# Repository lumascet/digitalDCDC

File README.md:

# Atmel atmega 328p DCDC controller
Arduino Uno Project for digitally controlling DCDC converter with adc & dac over i2c with dotmatrix display.
Utilizes the cheap B3606 analog DCDC converter circuit.

The onboard 4.096V reference in combination with 2 12bit DACs as well as one 4 Channel 16bit ADC enable accurate voltage and current setpoints. 

The graphical interface also features a graph display, showing voltage and current over time.

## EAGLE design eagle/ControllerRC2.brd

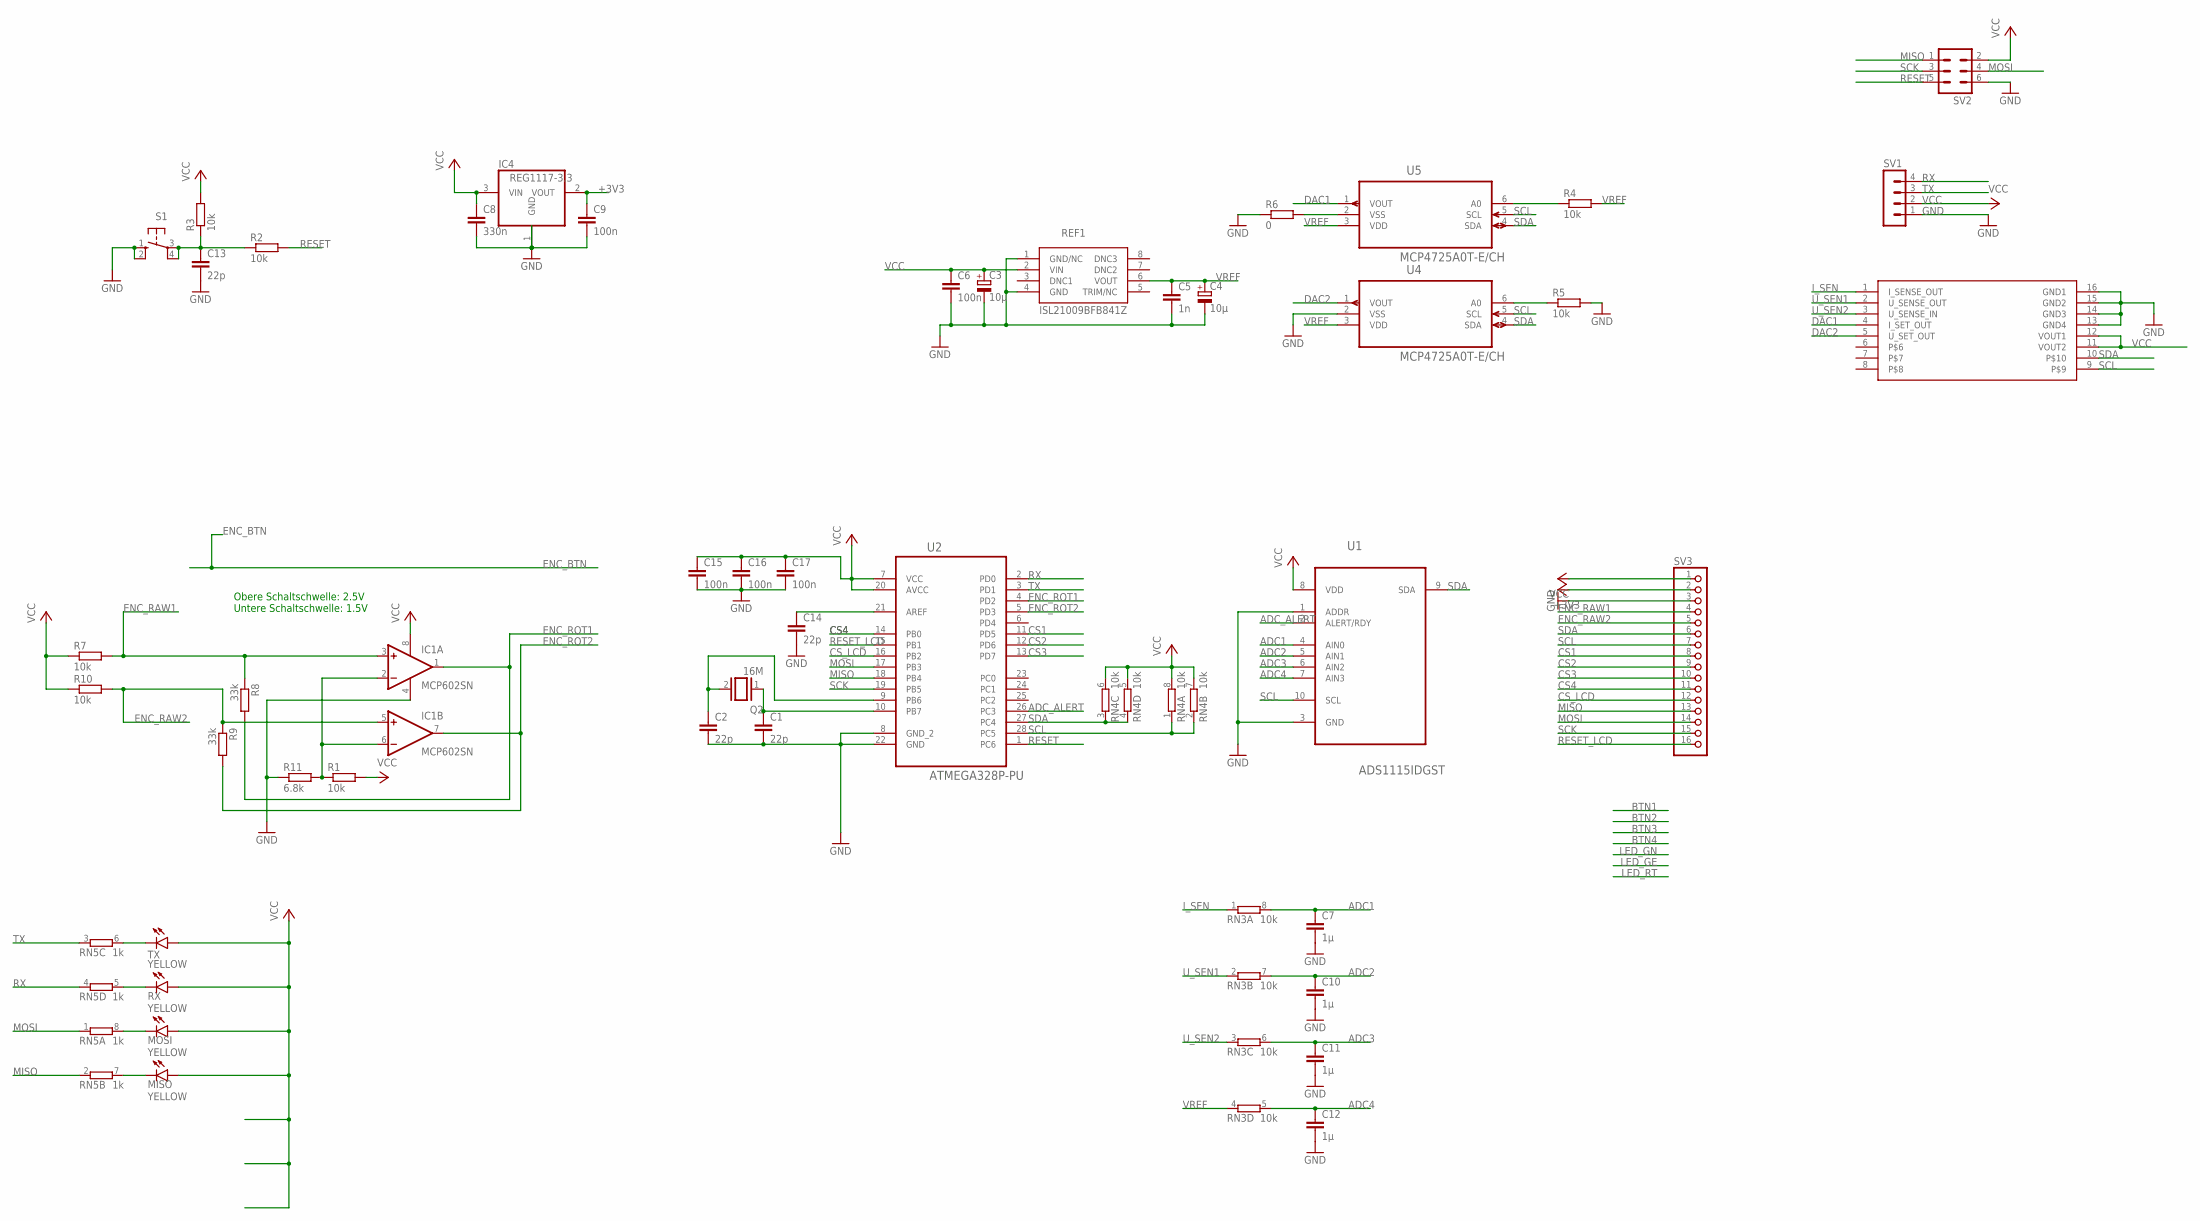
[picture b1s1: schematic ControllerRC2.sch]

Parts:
C1, C2, C13, C14: 22p; C0603
C3, C4: 10µ; E2,5-6E
C5: 1n; C0603
C6, C9, C15, C16, C17: 100n; C0603
C7, C10, C11, C12: 1µ; C0603
C8: 330n; C0603
IC1: MCP602SN; SO08
IC4: REG1117-3.3; SOT223
MISO: YELLOW; CHIP-LED0805
MOSI: YELLOW; CHIP-LED0805
Q2: 16M; QS
R1, R2, R3, R4, R5, R7, R10: 10k; R0603
R6: 0; R0603
R8, R9: 33k; R0603
R11: 6.8k; R0603
REF1: ISL21009BFB841Z; SOIC127P600X175-8N
RN3, RN4: 10k; 0603-ARC
RN5: 1k; 0603-ARC
RX: YELLOW; CHIP-LED0805
S1: 10-XX; B3F-10XX
SV1: MA04-1
SV2: MA03-2
SV3: PINHD-1X16; 1X16
TX: YELLOW; CHIP-LED0805
U1: ADS1115IDGST; SOP50P490X110-10N
U2: ATMEGA328P-PU; DIP254P762X457-28
U4, U5: MCP4725A0T-E/CH; SOT95P270X145-6N
U$1: DCPINHEADER; CDIP16

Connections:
+3V3: C9.1, IC4.2 (VOUT), SV3.2
ADC1: C7.1, RN3.8 (2), U1.4 (AIN0)
ADC2: C10.1, RN3.7 (2), U1.5 (AIN1)
ADC3: C11.1, RN3.6 (2), U1.6 (AIN2)
ADC4: C12.1, RN3.5 (2), U1.7 (AIN3)
ADC_ALERT: U1.2 (ALERT/RDY), U2.26 (PC3)
CS1: SV3.8, U2.11 (PD5)
CS2: SV3.9, U2.12 (PD6)
CS3: SV3.10, U2.13 (PD7)
CS4: SV3.11, U2.14 (PB0)
CS_LCD: SV3.12, U2.16 (PB2)
DAC1: U5.1 (VOUT), U$1.4 (I_SET_OUT)
DAC2: U4.1 (VOUT), U$1.5 (U_SET_OUT)
ENC_RAW1: IC1.3 (+IN), R7.2, R8.1, SV3.4
ENC_RAW2: IC1.5 (+IN), R9.1, R10.2, SV3.5
ENC_ROT1: IC1.1 (OUT), R8.2, U2.4 (PD2)
ENC_ROT2: IC1.7 (OUT), R9.2, U2.5 (PD3)
GND: C1.2, C2.2, C3.-, C4.-, C5.2, C6.2, C7.2, C8.2, C9.2, C10.2, C11.2, C12.2, C13.2, C14.2, C15.2, C16.2, C17.2, IC1.4 (V-), IC4.1 (GND), R5.2, R6.1, R11.1, REF1.1 (GND/NC), REF1.4 (GND), S1.1 (S), S1.2 (S1), SV1.1, SV2.6, SV3.3, U1.1 (ADDR), U1.3 (GND), U2.8 (GND_2), U2.22 (GND), U4.2 (VSS), U$1.13 (GND4), U$1.14 (GND3), U$1.15 (GND2), U$1.16 (GND1)
I_SEN: RN3.1, U$1.1 (I_SENSE_OUT)
MISO: RN5.2 (1), SV2.1, SV3.13, U2.18 (PB4)
MOSI: RN5.1, SV2.4, SV3.14, U2.17 (PB3)
unnamed: C1.1, Q2.1, U2.10 (PB7)
unnamed: RN5.6 (2), TX.C
unnamed: RN5.5 (2), RX.C
unnamed: MOSI.C, RN5.8 (2)
unnamed: MISO.C, RN5.7 (2)
unnamed: C2.1, Q2.2, U2.9 (PB6)
unnamed: C14.1, U2.21 (AREF)
unnamed: R4.1, U5.6 (A0)
unnamed: R5.1, U4.6 (A0)
unnamed: R6.2, U5.2 (VSS)
unnamed: IC1.2 (-IN), IC1.6 (-IN), R1.1, R11.2
unnamed: C13.1, R2.1, R3.1, S1.3, S1.4 (P1)
RESET: R2.2, SV2.5, U2.1 (PC6)
RESET_LCD: SV3.16, U2.15 (PB1)
RX: RN5.4 (1), SV1.4, U2.2 (PD0)
SCK: SV2.3, SV3.15, U2.19 (PB5)
SCL: RN4.1, RN4.2 (1), SV3.7, U1.10 (SCL), U2.28 (PC5), U4.5 (SCL), U5.5 (SCL), U$1.9
SDA: RN4.3 (1), RN4.4 (1), SV3.6, U1.9 (SDA), U2.27 (PC4), U4.4 (SDA), U5.4 (SDA), U$1.10
TX: RN5.3 (1), SV1.3, U2.3 (PD1)
U_SEN1: RN3.2 (1), U$1.2 (U_SENSE_OUT)
U_SEN2: RN3.3 (1), U$1.3 (U_SENSE_IN)
VCC: C3.+, C6.1, C8.1, C15.1, C16.1, C17.1, IC1.8 (V+), IC4.3 (VIN), MISO.A, MOSI.A, R1.2, R3.2, R7.1, R10.1, REF1.2 (VIN), RN4.5 (2), RN4.6 (2), RN4.7 (2), RN4.8 (2), RX.A, SV1.2, SV2.2, SV3.1, TX.A, U1.8 (VDD), U2.7 (VCC), U2.20 (AVCC), U$1.11 (VOUT2), U$1.12 (VOUT1)
VREF: C4.+, C5.1, R4.2, REF1.6 (VOUT), RN3.4 (1), U4.3 (VDD), U5.3 (VDD)

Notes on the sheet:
Obere Schaltschwelle: 2.5V Untere Schaltschwelle: 1.5V

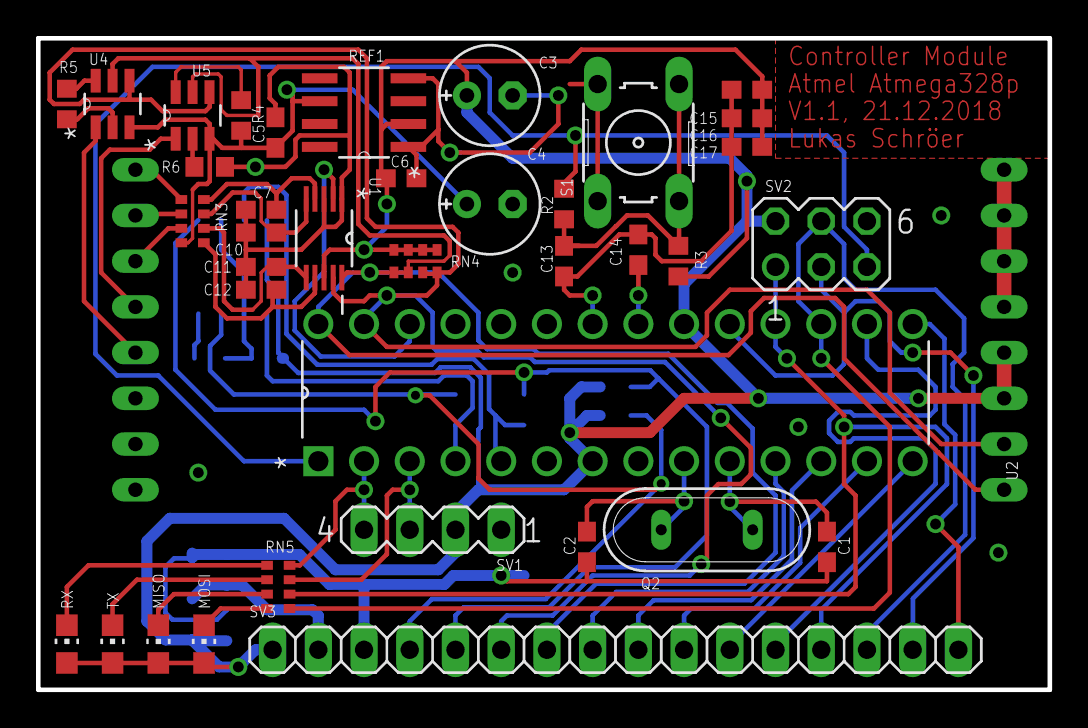
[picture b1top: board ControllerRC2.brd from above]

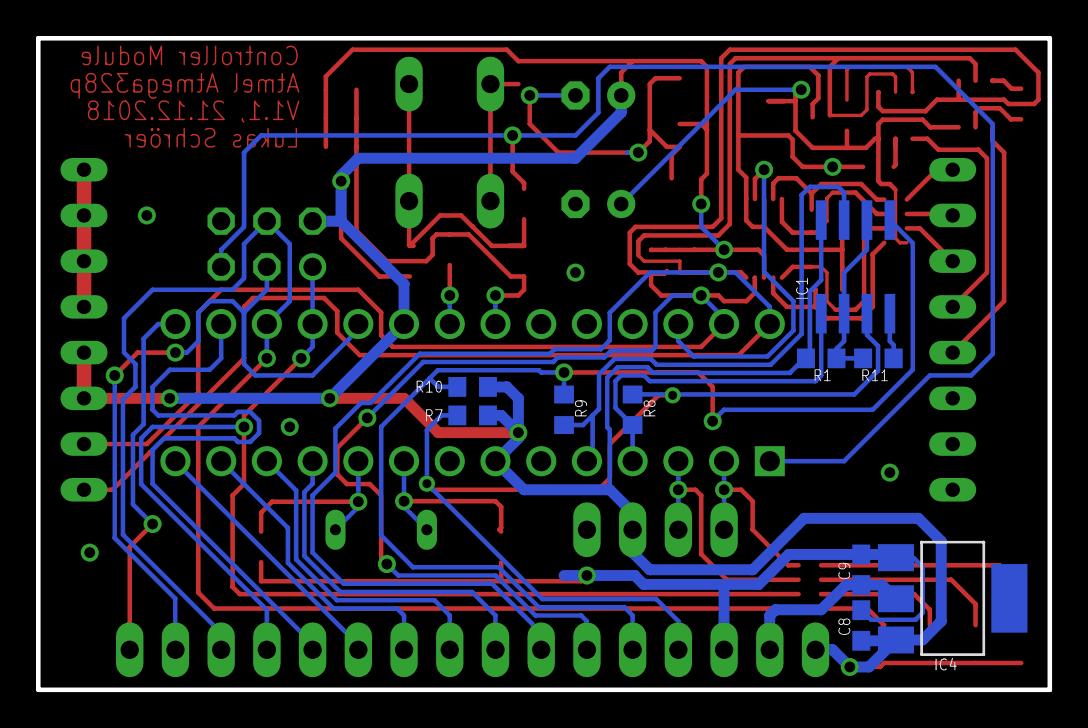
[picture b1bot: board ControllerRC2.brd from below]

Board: 2 copper layers, 56.2 x 36.2 mm, 48 parts (10 on the bottom side), 44 nets.

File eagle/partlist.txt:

Partlist

Exported from ControllerRC2.brd at 25.02.2019 17:07

EAGLE Version 9.2.2 Copyright (c) 1988-2018 Autodesk, Inc.

Assembly variant: 

Part     Value           Package            Library                                Position (inch)       Orientation

C1       22p             C0603              rcl                                    (2.6 2.0625)          R270
C2       22p             C0603              rcl                                    (2.075 2.0625)        R270
C3       10µ             E2,5-6E            rcl                                    (1.8625 3.05)         R0
C4       10µ             E2,5-6E            rcl                                    (1.8625 2.8125)       R0
C5       1n              C0603              rcl                                    (1.39375 2.96875)     R90
C6       100n            C0603              rcl                                    (1.66875 2.86875)     R0
C7       1µ              C0603              rcl                                    (1.3625 2.8)          R180
C8       330n            C0603              rcl                                    (1.2875 1.890625)     MR90
C9       100n            C0603              rcl                                    (1.2875 2.0125)       MR90
C10      1µ              C0603              rcl                                    (1.3625 2.75)         R180
C11      1µ              C0603              rcl                                    (1.3625 2.675)        R180
C12      1µ              C0603              rcl                                    (1.3625 2.625)        R180
C13      22p             C0603              rcl                                    (2.025 2.6875)        R270
C14      22p             C0603              rcl                                    (2.1875 2.7125)       R90
C15      100n            C0603              rcl                                    (2.425 3.0625)        R180
C16      100n            C0603              rcl                                    (2.425 3)             R180
C17      100n            C0603              rcl                                    (2.425 2.9375)        R180
IC1      MCP602SN        SO08               linear                                 (1.3 2.675)           MR0
IC4      REG1117-3.3     SOT223             burr-brown                             (1.0875 1.95)         MR270
MISO     YELLOW          CHIP-LED0805       led                                    (1.1375 1.85)         R0
MOSI     YELLOW          CHIP-LED0805       led                                    (1.2375 1.85)         R0
Q2       16M             QS                 special                                (2.3375 2.1)          R180
R1       10k             R0603              rcl                                    (1.375 2.475)         MR180
R2       10k             R0603              rcl                                    (2.025 2.8125)        R90
R3       10k             R0603              rcl                                    (2.275 2.6875)        R270
R4       10k             R0603              rcl                                    (1.31875 3.00625)     R270
R5       10k             R0603              rcl                                    (0.9375 3.03125)      R270
R6       0               R0603              rcl                                    (1.25 2.89375)        R180
R7       10k             R0603              rcl                                    (2.1375 2.35)         MR180
R8       33k             R0603              rcl                                    (1.7875 2.3625)       MR270
R9       33k             R0603              rcl                                    (1.9375 2.3625)       MR270
R10      10k             R0603              rcl                                    (2.1375 2.4125)       MR180
R11      6.8k            R0603              rcl                                    (1.25 2.475)          MR180
REF1     ISL21009BFB841Z SOIC127P600X175-8N custom                                 (1.5875 3.0125)       R180
RN3      10k             0603-ARC           resistor-dil                           (1.2125 2.775)        R270
RN4      10k             0603-ARC           resistor-dil                           (1.7 2.6875)          R0
RN5      1k              0603-ARC           resistor-dil                           (1.4 1.975)           R90
RX       YELLOW          CHIP-LED0805       led                                    (0.9375 1.85)         R0
S1                       B3F-10XX           switch-omron                           (2.1875 2.946875)     R90
SV1                      MA04-1             con-lstb                               (1.7375 2.1)          R180
SV2                      MA03-2             con-lstb                               (2.5875 2.725)        R0
SV3                      1X16               pinhead                                (2.1375 1.8375)       R0
TX       YELLOW          CHIP-LED0805       led                                    (1.0375 1.85)         R0
U$1      DCPINHEADER     CDIP16             custom                                 (2.0875 2.5875)       R0
U1       ADS1115IDGST    SOP50P490X110-10N  Texas Instruments_By_element14_Batch_1 (1.5 2.7375)          R270
U2       ATMEGA328P-PU   DIP254P762X457-28  Atmel_By_element14_Batch_1-00          (2.7875 2.55)         R90
U4       MCP4725A0T-E/CH SOT95P270X145-6N   Microchip_By_element14_Batch_1         (1.0375 3.03125)      R90
U5       MCP4725A0T-E/CH SOT95P270X145-6N   Microchip_By_element14_Batch_1         (1.2125 3.00625)      R90

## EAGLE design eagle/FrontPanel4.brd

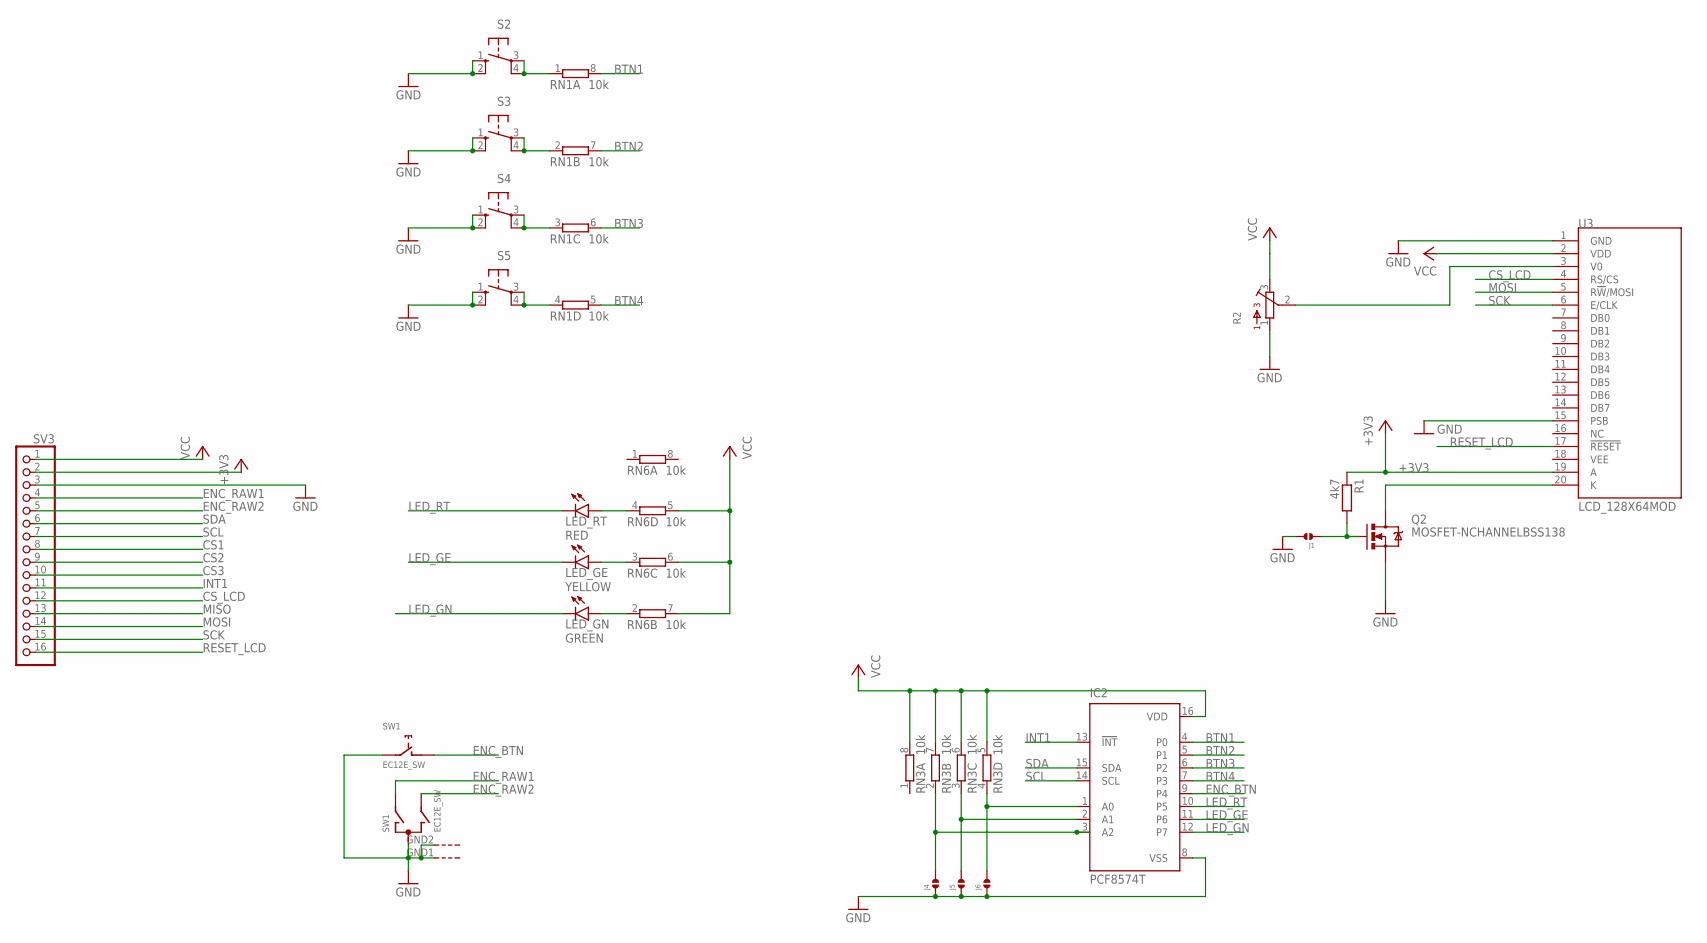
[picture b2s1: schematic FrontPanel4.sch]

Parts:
IC2: PCF8574T; SO16W
J1, J4, J5, J6: SOLDERJUMPER.2.MED; 2.MED
LED_GE: YELLOW; LED5MM
LED_GN: GREEN; LED5MM
LED_RT: RED; LED5MM
Q2: MOSFET-NCHANNELBSS138; SOT23
R1: 4k7; R1206
R2: 3362P
RN1, RN3, RN6: 10k; 0603-ARC
S2, S3, S4, S5: 10-XX; B3F-10XX
SV3: PINHD-1X16; 1X16
SW1: EC12E_SW; ALPS_EC12E_SW
U3: LCD_128X64MOD; LCD_128X64_MOD

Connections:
+3V3: R1.1, SV3.2, U3.19 (A)
BTN1: IC2.4 (P0), RN1.8 (2)
BTN2: IC2.5 (P1), RN1.7 (2)
BTN3: IC2.6 (P2), RN1.6 (2)
BTN4: IC2.7 (P3), RN1.5 (2)
CS1: SV3.8
CS2: SV3.9
CS3: SV3.10
CS_LCD: SV3.12, U3.4 (RS/CS)
ENC_BTN: IC2.9 (P4), SW1.D (1)
ENC_RAW1: SV3.4, SW1.A
ENC_RAW2: SV3.5, SW1.B
GND: IC2.8 (VSS), J1.2, J4.1, J5.1, J6.1, Q2.2 (S), R2.1, S2.1 (S), S2.2 (S1), S3.1 (S), S3.2 (S1), S4.1 (S), S4.2 (S1), S5.1 (S), S5.2 (S1), SV3.3, SW1.C, SW1.E (2), SW1.GND1 (G), SW1.GND2 (G), U3.1 (GND), U3.15 (PSB)
INT1: IC2.13 (!INT), SV3.11
LED_GE: IC2.11 (P6), LED_GE.K (C)
LED_GN: IC2.12 (P7), LED_GN.K (C)
LED_RT: IC2.10 (P5), LED_RT.K (C)
MISO: SV3.13
MOSI: SV3.14, U3.5 (R!W!/MOSI)
unnamed: R2.2, U3.3 (V0)
unnamed: RN1.1, S2.3, S2.4 (P1)
unnamed: RN1.2 (1), S3.3, S3.4 (P1)
unnamed: RN1.3 (1), S4.3, S4.4 (P1)
unnamed: RN1.4 (1), S5.3, S5.4 (P1)
unnamed: IC2.1 (A0), J6.2, RN3.4 (1)
unnamed: IC2.2 (A1), J5.2, RN3.3 (1)
unnamed: IC2.3 (A2), J4.2, RN3.2 (1)
unnamed: LED_RT.A, RN6.4 (1)
unnamed: LED_GE.A, RN6.3 (1)
unnamed: LED_GN.A, RN6.2 (1)
unnamed: Q2.3 (D), U3.20 (K)
unnamed: J1.1, Q2.1 (G), R1.2
RESET_LCD: SV3.16, U3.17 (!RESET!)
SCK: SV3.15, U3.6 (E/CLK)
SCL: IC2.14 (SCL), SV3.7
SDA: IC2.15 (SDA), SV3.6
VCC: IC2.16 (VDD), RN3.5 (2), RN3.6 (2), RN3.7 (2), RN3.8 (2), RN6.5 (2), RN6.6 (2), RN6.7 (2), SV3.1, U3.2 (VDD)

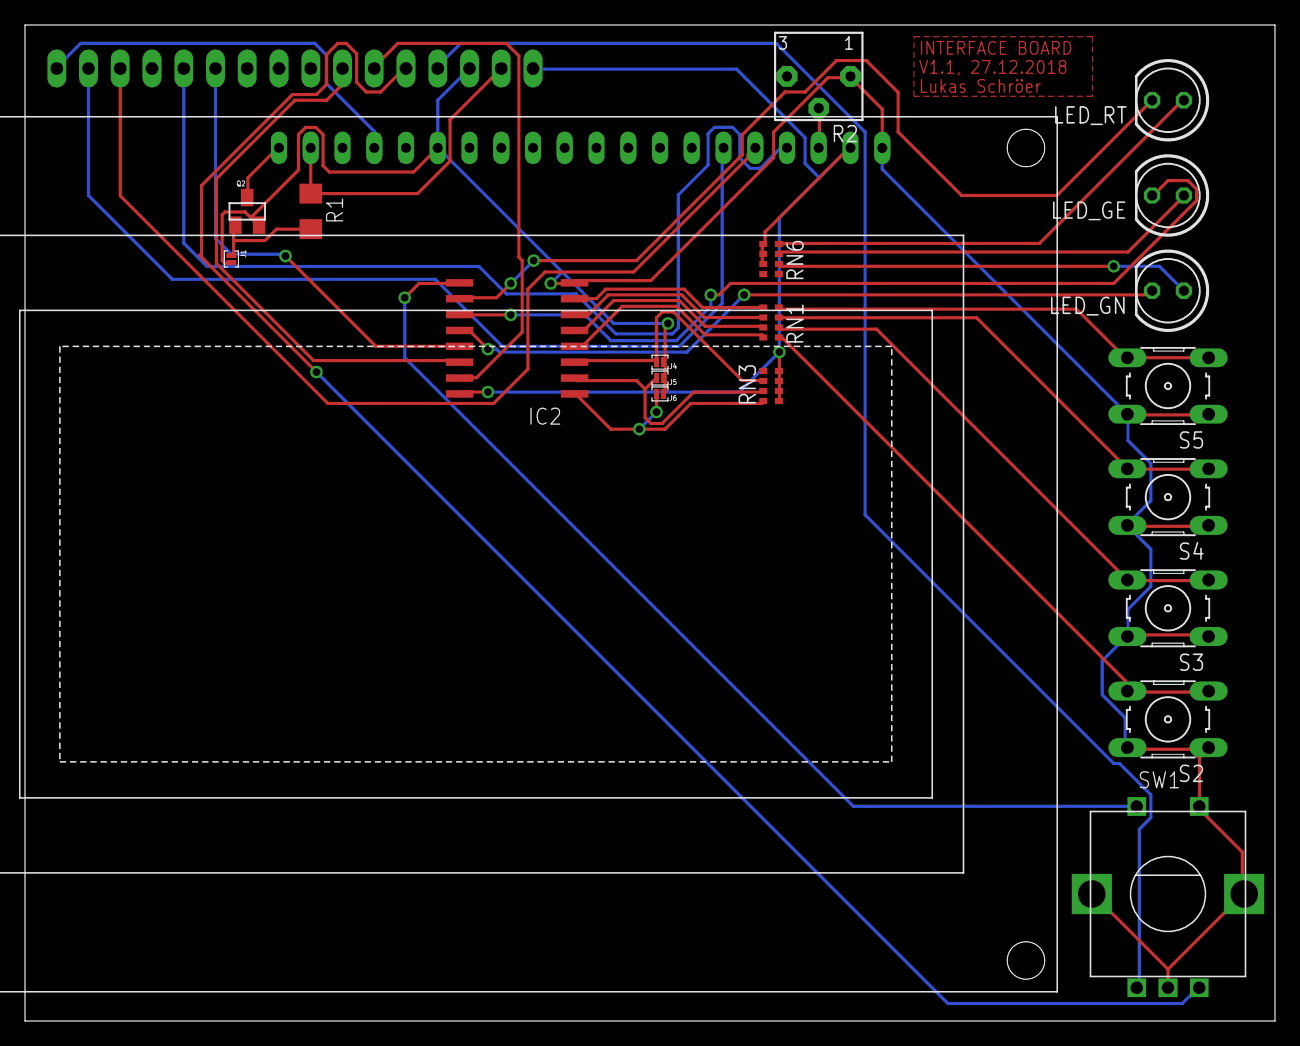
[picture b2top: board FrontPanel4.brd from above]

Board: 2 copper layers, 100.0 x 79.7 mm, 21 parts (1 on the bottom side), 33 nets.

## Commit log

2019-07-02 inital commit
2020-01-19 added description
2020-01-19 added board schematics
